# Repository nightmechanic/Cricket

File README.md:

# The Annoying Cricket

This is an attempt to build a MSP43G2230 based "annoying cricket" sound maker

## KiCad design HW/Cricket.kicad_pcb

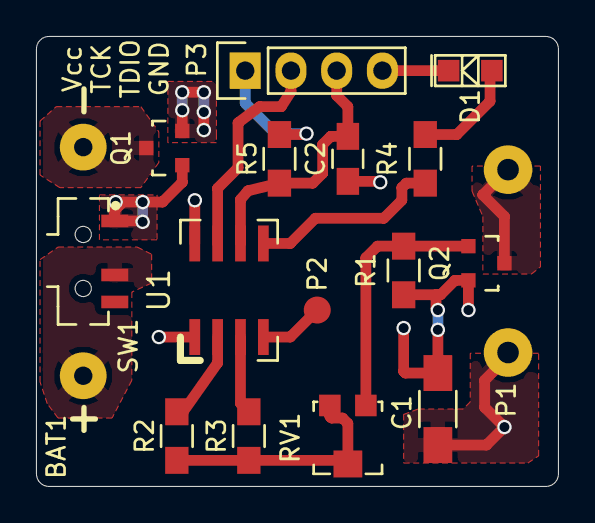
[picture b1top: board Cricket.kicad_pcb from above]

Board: 2 copper layers, 29.0 x 25.0 mm, 17 parts (0 on the bottom side), 14 nets.

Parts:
BAT1: Keystone_2468_2xAAA; Keystone_2468_no_mnt_holes
C1: 10uF 10V; C_1206_HandSoldering
C2: 1.8nF; C_0805_HandSoldering
D1: Orange LED; SMD_MiniLED
P1: CONN_01X02; WireConnection_1.20mmDrill
P2: CONN_01X01; Measurement_Point_Round-SMD-Pad_Small
P3: CONN_01X04; Pin_Header_Straight_1x04
Q1: Si2312CDS; SOT-23
Q2: Q_NPN_BEC; SOT-23
R1, R2, R3: 1k; R_0805_HandSoldering
R4: 330R; R_0805_HandSoldering
R5: 47k; R_0805_HandSoldering
RV1: 3.3k POT; Bourns_TC33X_2
SW1: SPDT_SLIDE; ALPS_SSSS810701
U1: MSP430G2230ID; TI-D-SOIC-8

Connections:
/Bat+: BAT1.1, SW1.2
/Bat-: BAT1.2, Q1.3
/SBWTCK: P3.2, U1.7
/SBWTDIO: C2.1, P3.3, R5.2, U1.6
GND: C1.2, C2.2, D1.2, P3.4, Q1.2, Q2.2, R1.1, U1.8
unnamed: D1.1, R4.2
unnamed: P1.1, Q2.3
unnamed: P2.1, U1.4
unnamed: Q2.1, R1.2, RV1.1
unnamed: R2.1, U1.2
unnamed: R2.2, R3.2, RV1.2, RV1.3
unnamed: R3.1, U1.3
unnamed: R4.1, U1.5
V_Batt: C1.1, P1.2, P3.1, Q1.1, R5.1, SW1.1, U1.1

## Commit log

2016-08-28 Verrsion 0.1
    Code written, complies, not checked in any way..
2016-08-28 Revert "Verrsion 0.1"
    This reverts commit d973fac8c74aaf63ab570f7c77f995105a996662.
2016-08-28 Version 0.1
    Written, compiles (on CCS 6.1), not tested on any HW
2016-09-05 First draft of schematics and layout
2016-09-05 layout finished, gerbers etc.
2016-09-07 reduce solder make expansion
2016-09-11 full CCS v6 project
2016-09-11 Added Vbat value blinking
2016-09-13 gitignore update
2016-09-13 corrected V_frac calculation
2016-09-13 stack size change
2016-09-20 changed all timer macros to TA0xxx
2016-09-22 support for msp430g2553 launchpad fixed VLO cal
2017-01-02 Increased sleep, vbat blink
    - Added delay before first vbat bilnk
    - Increased sleep periods to be between 1:00 and 4:20

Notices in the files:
HW/Cricket.kicad_pcb:
©Nightmechanic
